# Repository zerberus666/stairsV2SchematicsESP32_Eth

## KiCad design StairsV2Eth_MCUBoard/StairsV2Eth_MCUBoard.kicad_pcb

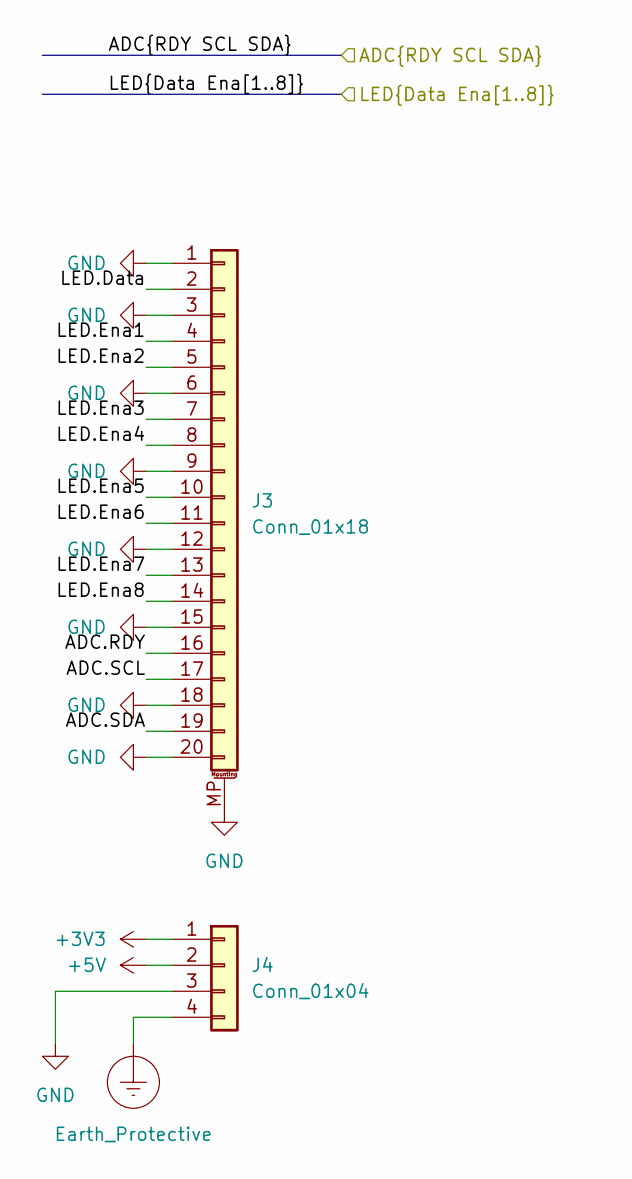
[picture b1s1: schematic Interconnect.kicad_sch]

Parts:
J3: Conn_01x18; FPC0520A1-20PVSZS1
J4: Conn_01x04; JST_XH_B4B-XH-AM_1x04_P2.50mm_Vertical

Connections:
+3V3: J4.1; also elsewhere on the board
+5V: J4.2
/ADC.RDY: J3.16
/ADC.SCL: J3.17
/ADC.SDA: J3.19
/LED.Data: J3.2; also elsewhere on the board
/LED.Ena1: J3.4; also elsewhere on the board
/LED.Ena2: J3.5; also elsewhere on the board
/LED.Ena3: J3.7; also elsewhere on the board
/LED.Ena4: J3.8; also elsewhere on the board
/LED.Ena5: J3.10; also elsewhere on the board
/LED.Ena6: J3.11; also elsewhere on the board
/LED.Ena7: J3.13; also elsewhere on the board
/LED.Ena8: J3.14; also elsewhere on the board
Earth_Protective: J4.4; also elsewhere on the board
GND: J3.1, J3.3, J3.6, J3.9, J3.12, J3.15, J3.18, J3.20, J3.MP (MountPin), J4.3; also elsewhere on the board

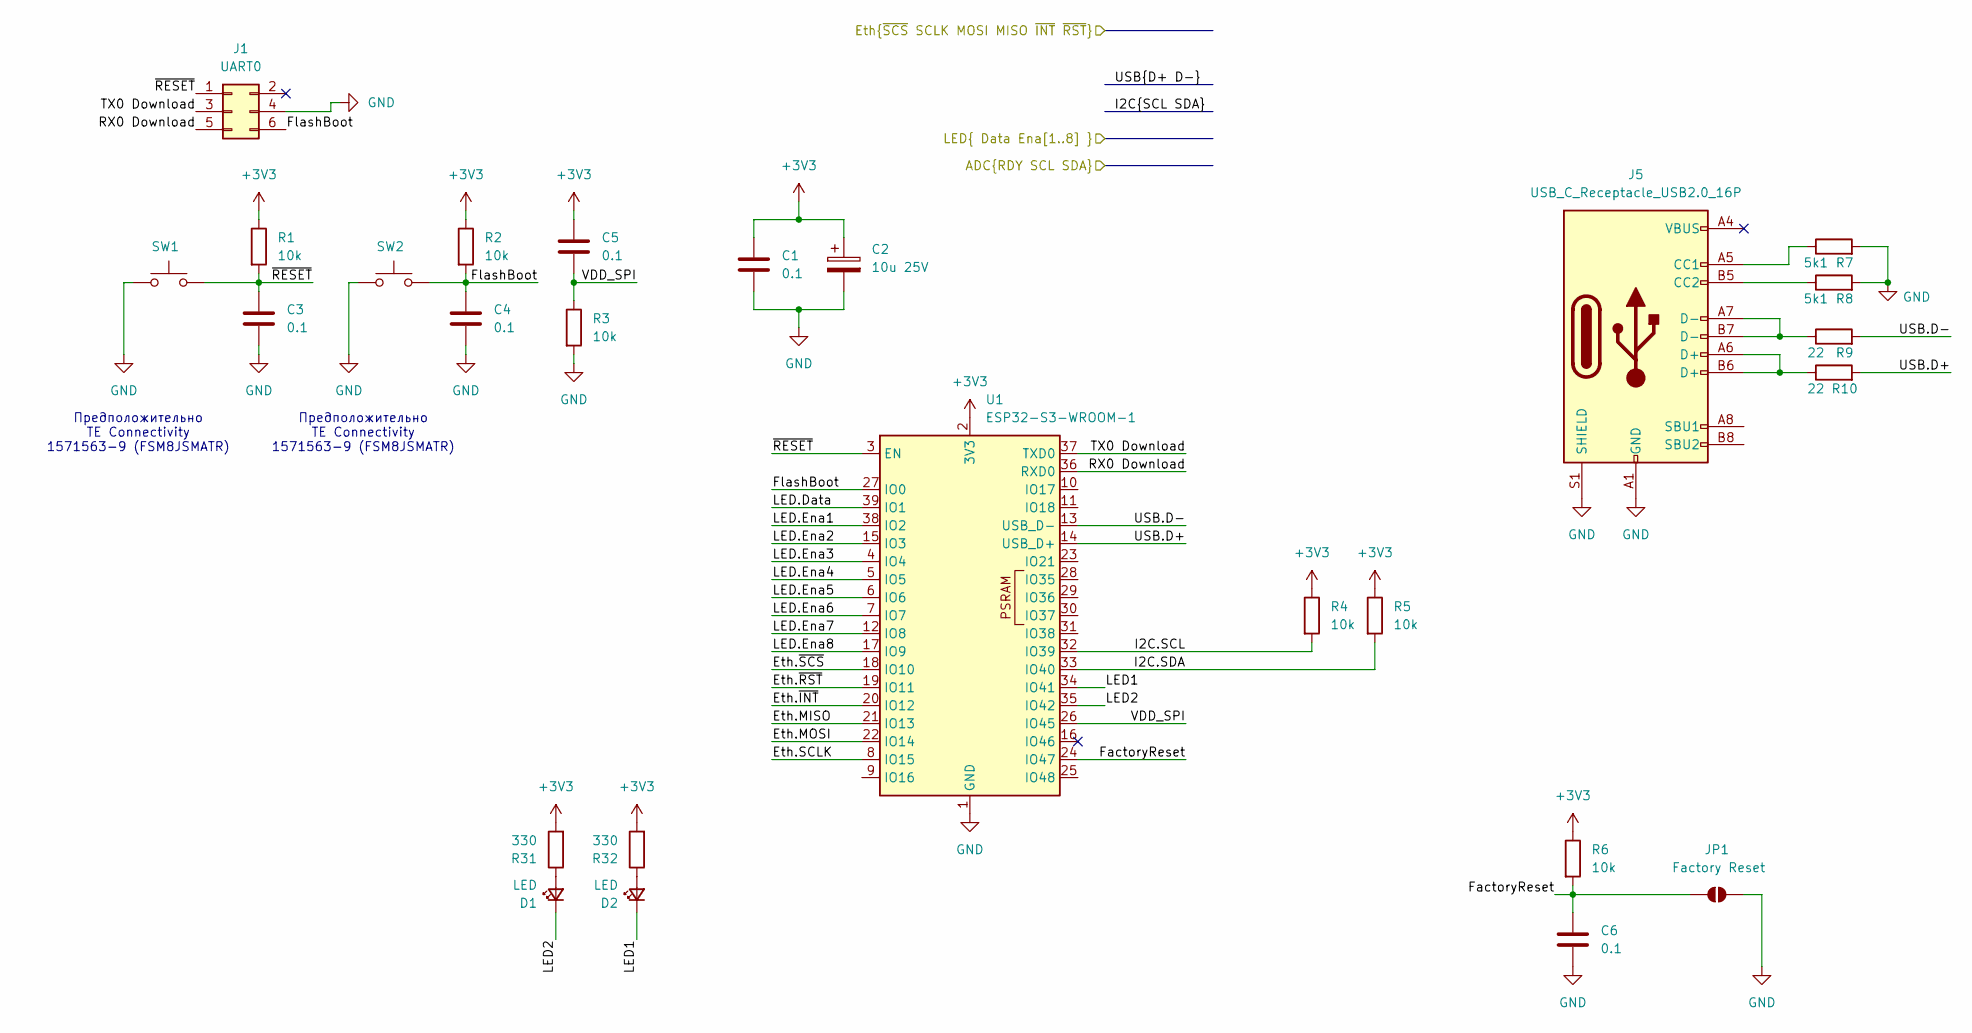
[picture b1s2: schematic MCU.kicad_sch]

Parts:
C1, C3, C4, C5, C6: 0.1; C_0805_2012Metric
C2: 10u 25V; CP_Elec_4x5.4
D1, D2: LED; LED_D3.0mm
J1: UART0; PinHeader_2x03_P1.27mm_Vertical_SMD
J5: USB_C_Receptacle_USB2.0_16P; USB_C_Receptacle_GCT_USB4110
JP1: Factory Reset; SolderJumper-2_P1.3mm_Open_RoundedPad1.0x1.5mm
R1, R2, R3, R4, R5, R6: 10k; R_0805_2012Metric
R7, R8: 5k1; R_0805_2012Metric
R9, R10: 22; R_0805_2012Metric
R31, R32: 330; R_0805_2012Metric
SW1, SW2: SW_Push; SW_Push_1P1T_NO_CK_KSC9xxJ
U1: ESP32-S3-WROOM-1

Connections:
+3V3: C1.1, C2.1, C5.1, R1.1, R2.1, R4.1, R5.1, R6.1, R31.2, R32.2, U1.2 (3V3); also elsewhere on the board
/Eth.MISO: U1.21 (IO13); also elsewhere on the board
/Eth.MOSI: U1.22 (IO14); also elsewhere on the board
/Eth.SCLK: U1.8 (IO15); also elsewhere on the board
/Eth.~INT: U1.20 (IO12); also elsewhere on the board
/Eth.~RST: U1.19 (IO11); also elsewhere on the board
/Eth.~SCS: U1.18 (IO10); also elsewhere on the board
/LED.Data: U1.39 (IO1); also elsewhere on the board
/LED.Ena1: U1.38 (IO2); also elsewhere on the board
/LED.Ena2: U1.15 (IO3); also elsewhere on the board
/LED.Ena3: U1.4 (IO4); also elsewhere on the board
/LED.Ena4: U1.5 (IO5); also elsewhere on the board
/LED.Ena5: U1.6 (IO6); also elsewhere on the board
/LED.Ena6: U1.7 (IO7); also elsewhere on the board
/LED.Ena7: U1.12 (IO8); also elsewhere on the board
/LED.Ena8: U1.17 (IO9); also elsewhere on the board
/MCU/FactoryReset: C6.1, JP1.1 (A), R6.2, U1.24 (IO47)
/MCU/FlashBoot: C4.1, J1.6, R2.2, SW2.2, U1.27 (IO0)
/MCU/I2C.SCL: R4.2, U1.32 (IO39)
/MCU/I2C.SDA: R5.2, U1.33 (IO40)
/MCU/LED1: D2.1 (K), U1.34 (IO41)
/MCU/LED2: D1.1 (K), U1.35 (IO42)
/MCU/RX0 Download: J1.5, U1.36 (RXD0)
/MCU/TX0 Download: J1.3, U1.37 (TXD0)
/MCU/USB.D+: R10.2, U1.14 (USB_D+)
/MCU/USB.D-: R9.2, U1.13 (USB_D-)
/MCU/VDD_SPI: C5.2, R3.1, U1.26 (IO45)
/MCU/~RESET: C3.1, J1.1, R1.2, SW1.2, U1.3 (EN)
GND: C1.2, C2.2, C3.2, C4.2, C6.2, J1.4, J5.A1 (GND), J5.A12 (GND), J5.B1 (GND), J5.B12 (GND), J5.S1 (SHIELD), JP1.2 (B), R3.2, R7.2, R8.2, SW1.1, SW2.1, U1.1 (GND), U1.40 (GND), U1.41 (GND); also elsewhere on the board
unnamed: D1.2 (A), R31.1
unnamed: D2.2 (A), R32.1
unnamed: J5.A5 (CC1), R7.1
unnamed: J5.B5 (CC2), R8.1
unnamed: J5.A6 (D+), J5.B6 (D+), R10.1
unnamed: J5.A7 (D-), J5.B7 (D-), R9.1

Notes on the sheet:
Предположительно TE Connectivity 1571563-9 (FSM8JSMATR)

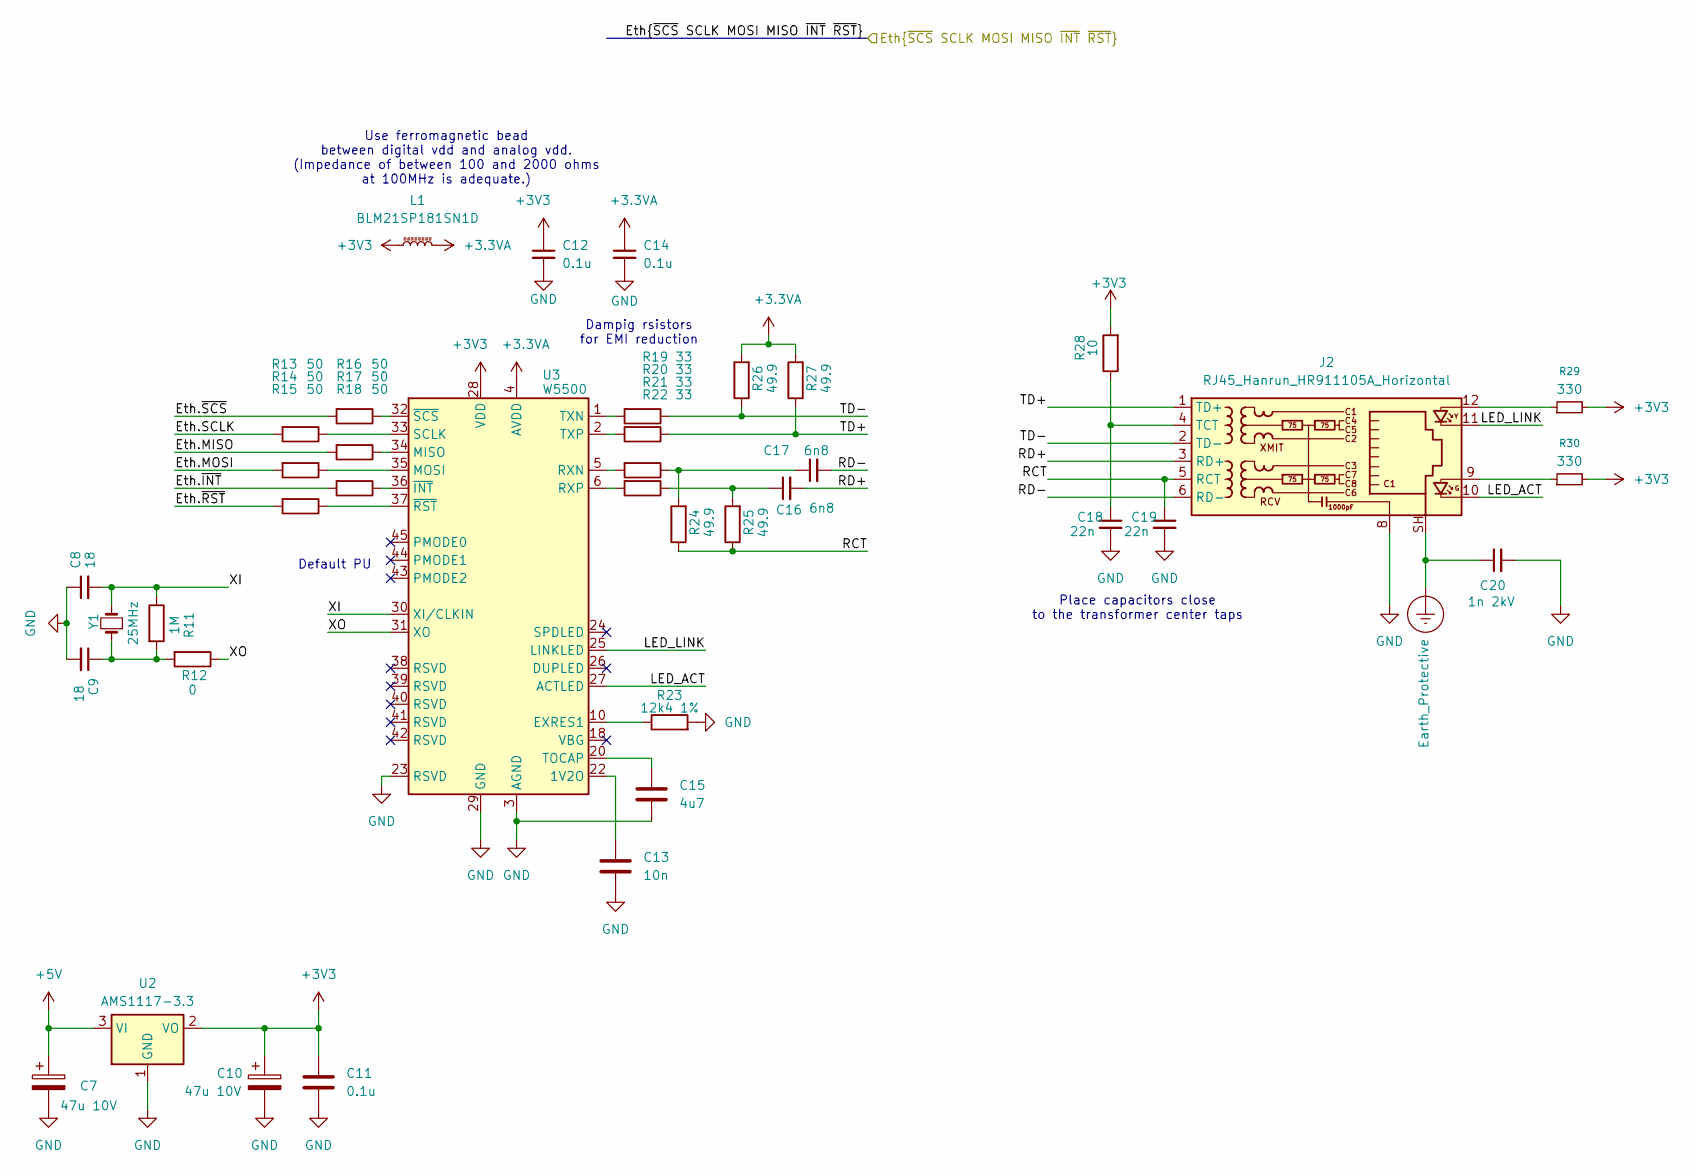
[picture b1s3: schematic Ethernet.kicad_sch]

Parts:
C7, C10: 47u 10V; CP_Elec_5x5.4
C8, C9: 18; C_0805_2012Metric
C11, C12, C14: 0.1u; C_0805_2012Metric
C13: 10n; C_0805_2012Metric
C15: 4u7; C_0805_2012Metric
C16, C17: 6n8; C_0805_2012Metric
C18, C19: 22n; C_0805_2012Metric
C20: 1n 2kV; C_Disc_D7.5mm_W2.5mm_P5.00mm
J2: RJ45_Hanrun_HR911105A_Horizontal
L1: BLM21SP181SN1D; L_0805_2012Metric
R11: 1M; R_0805_2012Metric
R12: 0; R_0805_2012Metric
R13, R14, R15, R16, R17, R18: 50; R_0805_2012Metric
R19, R20, R21, R22: 33; R_0805_2012Metric
R23: 12k4 1%; R_0805_2012Metric
R24, R25, R26, R27: 49.9; R_0805_2012Metric
R28: 10; R_0805_2012Metric
R29, R30: 330; R_0805_2012Metric
U2: AMS1117-3.3; SOT-223-3_TabPin2
U3: W5500; LQFP-48_7x7mm_P0.5mm
Y1: 25MHz; Crystal_SMD_Qantek_QC5CB-2Pin_5x3.2mm

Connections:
+3.3VA: C14.1, L1.2, R26.2, R27.2, U3.4 (AVDD), U3.8 (AVDD), U3.11 (AVDD), U3.15 (AVDD), U3.17 (AVDD), U3.21 (AVDD)
+3V3: C10.1, C11.1, C12.1, L1.1, R28.2, R29.2, R30.2, U2.2 (VO), U3.28 (VDD); also elsewhere on the board
/Eth.MISO: R17.2; also elsewhere on the board
/Eth.MOSI: R14.2; also elsewhere on the board
/Eth.SCLK: R13.2; also elsewhere on the board
/Eth.~INT: R18.2; also elsewhere on the board
/Eth.~RST: R15.2; also elsewhere on the board
/Eth.~SCS: R16.2; also elsewhere on the board
/Ethernet/LED_ACT: J2.10, U3.27 (ACTLED)
/Ethernet/LED_LINK: J2.11, U3.25 (LINKLED)
/Ethernet/RCT: C19.1, J2.5 (RCT), R24.1, R25.1
/Ethernet/RD+: C16.2, J2.3 (RD+)
/Ethernet/RD-: C17.2, J2.6 (RD-)
/Ethernet/TD+: J2.1 (TD+), R20.1, R27.1
/Ethernet/TD-: J2.2 (TD-), R19.1, R26.1
/Ethernet/XI: C8.2, R11.1, U3.30 (XI/CLKIN), Y1.2
/Ethernet/XO: R12.1, U3.31 (XO)
Earth_Protective: C20.1, J2.SH; also elsewhere on the board
GND: C7.2, C8.1, C9.2, C10.2, C11.2, C12.2, C13.2, C14.2, C15.2, C18.2, C19.2, C20.2, J2.8, R23.2, U2.1 (GND), U3.3 (AGND), U3.9 (AGND), U3.14 (AGND), U3.16 (AGND), U3.19 (AGND), U3.23 (RSVD), U3.29 (GND), U3.48 (AGND); also elsewhere on the board
unnamed: C7.1, U2.3 (VI)
unnamed: C9.1, R11.2, R12.2, Y1.1
unnamed: C16.1, R22.1, R25.2
unnamed: C17.1, R21.1, R24.2
unnamed: J2.9, R30.1
unnamed: J2.12, R29.1
unnamed: C18.1, J2.4 (TCT), R28.1
unnamed: C13.1, U3.22 (1V2O)
unnamed: R23.1, U3.10 (EXRES1)
unnamed: R17.1, U3.34 (MISO)
unnamed: R14.1, U3.35 (MOSI)
unnamed: R21.2, U3.5 (RXN)
unnamed: R22.2, U3.6 (RXP)
unnamed: R13.1, U3.33 (SCLK)
unnamed: C15.1, U3.20 (TOCAP)
unnamed: R19.2, U3.1 (TXN)
unnamed: R20.2, U3.2 (TXP)
unnamed: R18.1, U3.36 (~INT)
unnamed: R15.1, U3.37 (~RST)
unnamed: R16.1, U3.32 (~SCS)

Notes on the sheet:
Dampig rsistors for EMI reduction
Use ferromagnetic bead between digital vdd and analog vdd. (Impedance of between 100 and 2000 ohms at 100MHz is adequate.)
Place capacitors close to the transformer center taps
Default PU

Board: 2 copper layers, 61 parts (57 on the bottom side), 65 nets, no tracks yet.

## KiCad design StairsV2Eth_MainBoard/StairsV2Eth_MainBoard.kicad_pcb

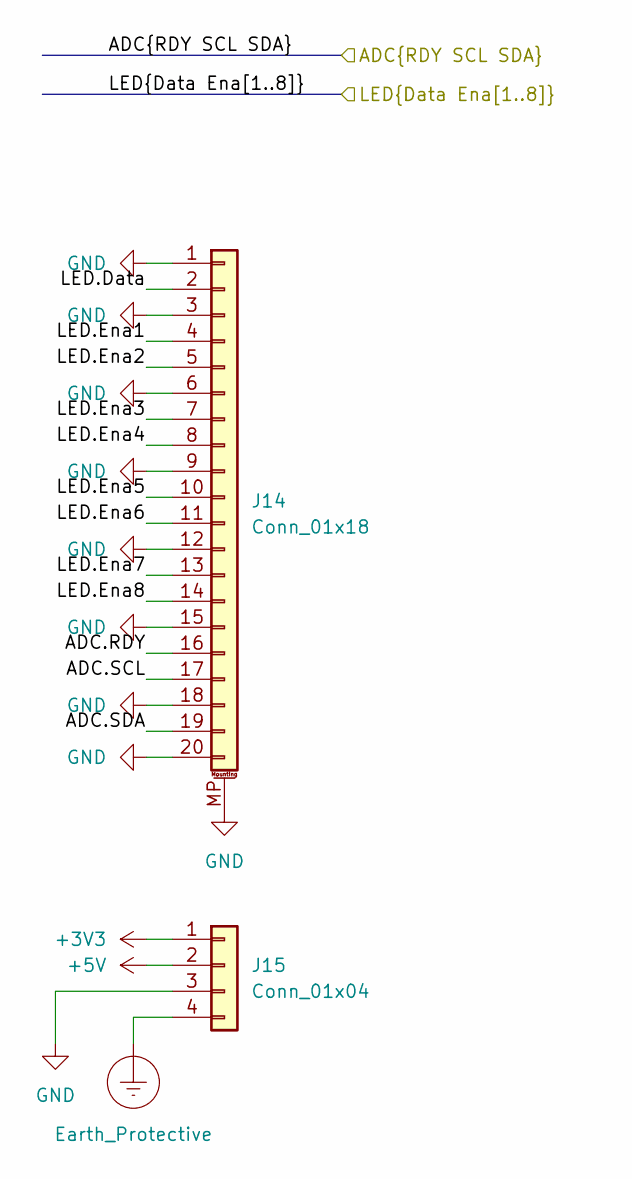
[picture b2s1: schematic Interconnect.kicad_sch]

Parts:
J14: Conn_01x18; FPC0520A1-20PVSZS1
J15: Conn_01x04; JST_XH_B4B-XH-AM_1x04_P2.50mm_Vertical

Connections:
+3V3: J15.1; also elsewhere on the board
+5V: J15.2; also elsewhere on the board
/ADC.RDY: J14.16; also elsewhere on the board
/ADC.SCL: J14.17; also elsewhere on the board
/ADC.SDA: J14.19; also elsewhere on the board
/LED.Data: J14.2; also elsewhere on the board
/LED.Ena1: J14.4; also elsewhere on the board
/LED.Ena2: J14.5; also elsewhere on the board
/LED.Ena3: J14.7; also elsewhere on the board
/LED.Ena4: J14.8; also elsewhere on the board
/LED.Ena5: J14.10; also elsewhere on the board
/LED.Ena6: J14.11; also elsewhere on the board
/LED.Ena7: J14.13; also elsewhere on the board
/LED.Ena8: J14.14; also elsewhere on the board
Earth_Protective: J15.4; also elsewhere on the board
GND: J14.1, J14.3, J14.6, J14.9, J14.12, J14.15, J14.18, J14.20, J14.MP (MountPin), J15.3; also elsewhere on the board

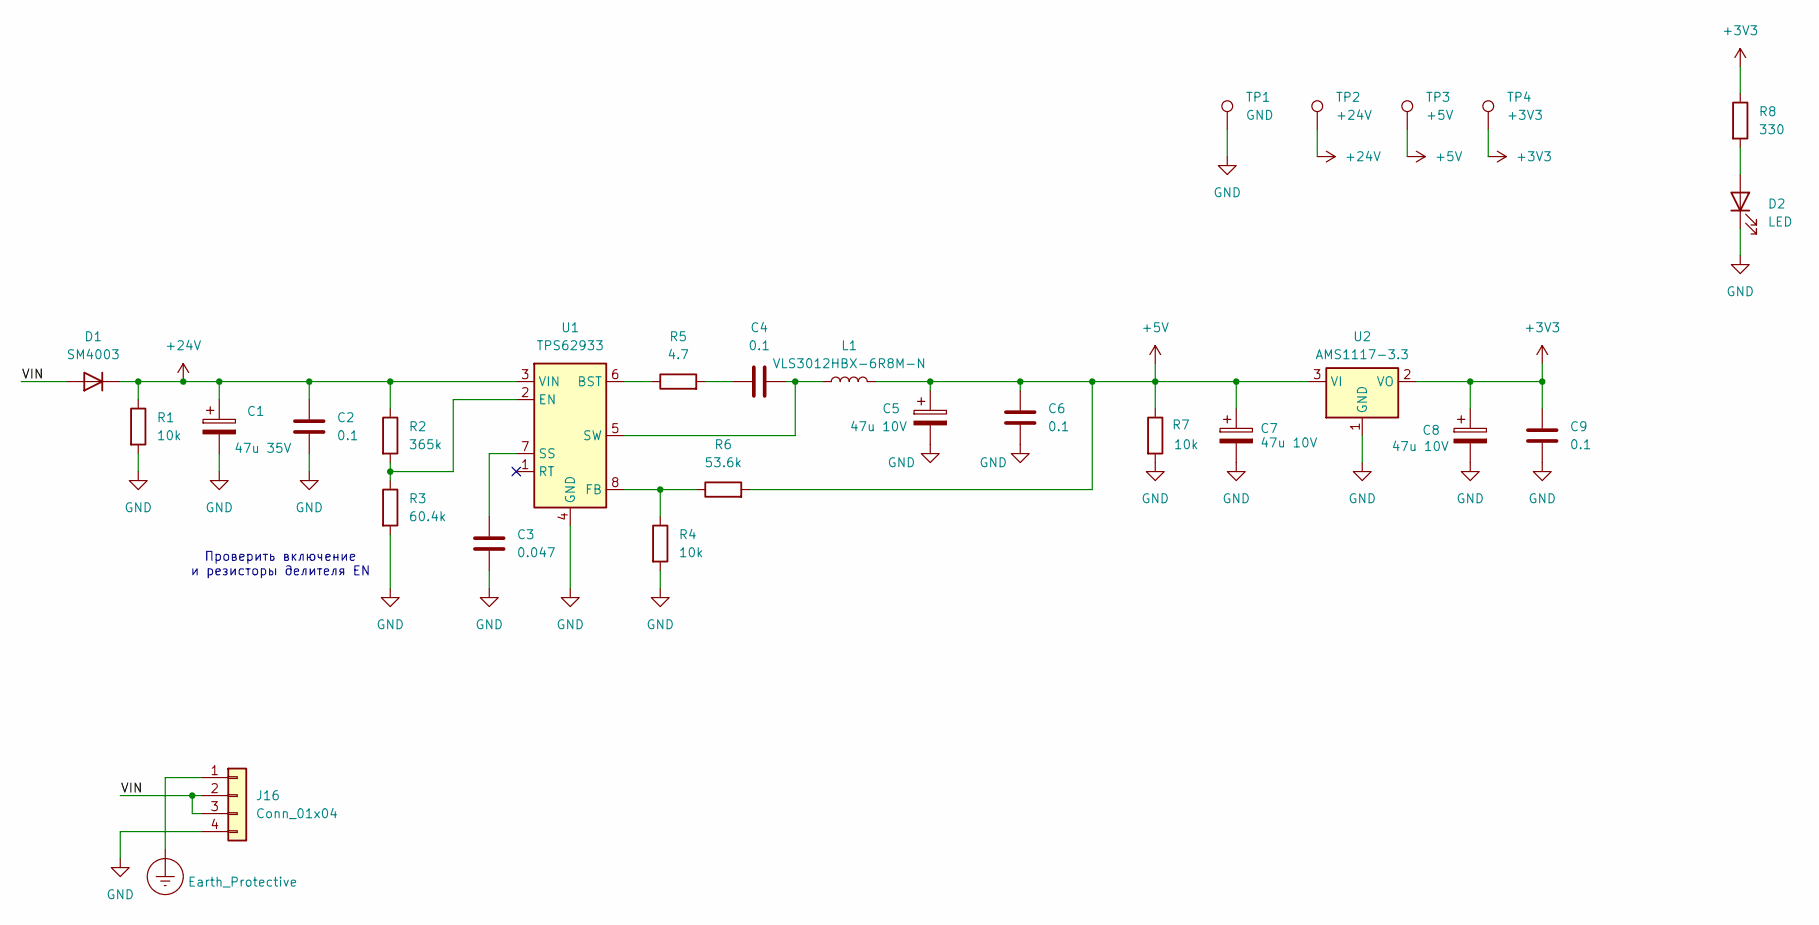
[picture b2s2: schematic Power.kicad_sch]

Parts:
C1: 47u 35V; CP_Elec_6.3x5.4
C2, C4, C6, C9: 0.1; C_0805_2012Metric
C3: 0.047; C_0805_2012Metric
C5, C7, C8: 47u 10V; CP_Elec_5x5.4
D1: SM4003; D_MELF
D2: LED; LED_0805_2012Metric
J16: Conn_01x04; PhoenixContact_MCV_1,5_4-G-3.5_1x04_P3.50mm_Vertical
L1: VLS3012HBX-6R8M-N; IND_VLS3012HBX-6R8M-N
R1, R4, R7: 10k; R_0805_2012Metric
R2: 365k; R_0805_2012Metric
R3: 60.4k; R_0805_2012Metric
R5: 4.7; R_0805_2012Metric
R6: 53.6k; R_0805_2012Metric
R8: 330; R_0805_2012Metric
TP1: GND; TestPoint_Pad_1.0x1.0mm
TP2: +24V; TestPoint_Pad_1.0x1.0mm
TP3: +5V; TestPoint_Pad_1.0x1.0mm
TP4: +3V3; TestPoint_Pad_1.0x1.0mm
U1: TPS62933; SOT-583-8
U2: AMS1117-3.3; SOT-223-3_TabPin2

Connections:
+3V3: C8.1, C9.1, R8.1, TP4.1, U2.2 (VO); also elsewhere on the board
+5V: C5.1, C6.1, C7.1, L1.2, R6.2, R7.1, TP3.1, U2.3 (VI); also elsewhere on the board
+24V: C1.1, C2.1, D1.1 (K), R1.1, R2.1, TP2.1, U1.3 (VIN); also elsewhere on the board
/Power/VIN: D1.2 (A), J16.2, J16.3
Earth_Protective: J16.1; also elsewhere on the board
GND: C1.2, C2.2, C3.2, C5.2, C6.2, C7.2, C8.2, C9.2, D2.1 (K), J16.4, R1.2, R3.2, R4.2, R7.2, TP1.1, U1.4 (GND), U2.1 (GND); also elsewhere on the board
unnamed: C4.1, R5.2
unnamed: D2.2 (A), R8.2
unnamed: R5.1, U1.6 (BST)
unnamed: R2.2, R3.1, U1.2 (EN)
unnamed: R4.1, R6.1, U1.8 (FB)
unnamed: C3.1, U1.7 (SS)
unnamed: C4.2, L1.1, U1.5 (SW)

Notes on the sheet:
Проверить включение и резисторы делителя EN

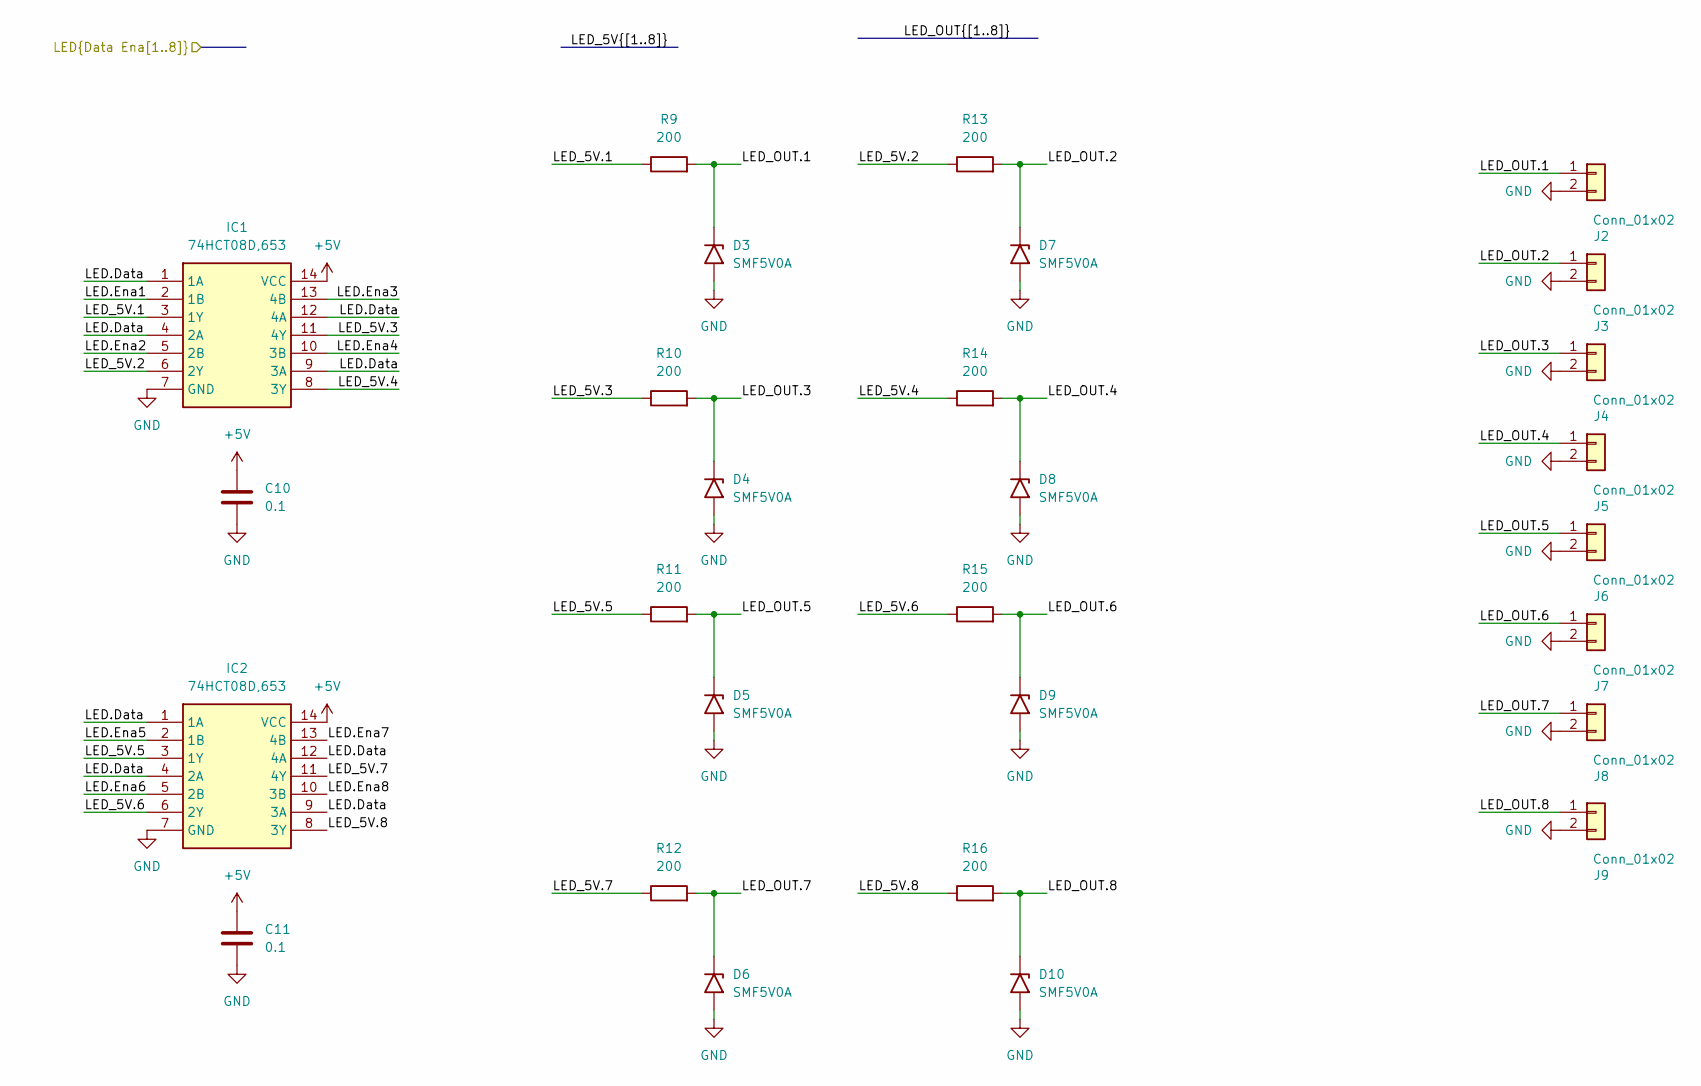
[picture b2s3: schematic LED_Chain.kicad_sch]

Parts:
C10, C11: 0.1; C_0805_2012Metric
D3, D4, D5, D6, D7, D8, D9, D10: SMF5V0A; D_SMF
IC1, IC2: 74HCT08D,653; SOIC127P600X175-14N; Manufacturer_Part_Number 74HCT08D,653; Mouser Part Number 771-74HCT08D-T
J2, J3, J4, J5, J6, J7, J8, J9: Conn_01x02; PhoenixContact_MCV_1,5_2-G-3.5_1x02_P3.50mm_Vertical
R9, R10, R11, R12, R13, R14, R15, R16: 200; R_0805_2012Metric

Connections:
+5V: C10.1, C11.1, IC1.14 (VCC), IC2.14 (VCC); also elsewhere on the board
/LED Chain/LED_5V.1: IC1.3 (1Y), R9.1
/LED Chain/LED_5V.2: IC1.6 (2Y), R13.1
/LED Chain/LED_5V.3: IC1.11 (4Y), R10.1
/LED Chain/LED_5V.4: IC1.8 (3Y), R14.1
/LED Chain/LED_5V.5: IC2.3 (1Y), R11.1
/LED Chain/LED_5V.6: IC2.6 (2Y), R15.1
/LED Chain/LED_5V.7: IC2.11 (4Y), R12.1
/LED Chain/LED_5V.8: IC2.8 (3Y), R16.1
/LED Chain/LED_OUT.1: D3.1 (A1), J2.1, R9.2
/LED Chain/LED_OUT.2: D7.1 (A1), J3.1, R13.2
/LED Chain/LED_OUT.3: D4.1 (A1), J4.1, R10.2
/LED Chain/LED_OUT.4: D8.1 (A1), J5.1, R14.2
/LED Chain/LED_OUT.5: D5.1 (A1), J6.1, R11.2
/LED Chain/LED_OUT.6: D9.1 (A1), J7.1, R15.2
/LED Chain/LED_OUT.7: D6.1 (A1), J8.1, R12.2
/LED Chain/LED_OUT.8: D10.1 (A1), J9.1, R16.2
/LED.Data: IC1.1 (1A), IC1.4 (2A), IC1.9 (3A), IC1.12 (4A), IC2.1 (1A), IC2.4 (2A), IC2.9 (3A), IC2.12 (4A); also elsewhere on the board
/LED.Ena1: IC1.2 (1B); also elsewhere on the board
/LED.Ena2: IC1.5 (2B); also elsewhere on the board
/LED.Ena3: IC1.13 (4B); also elsewhere on the board
/LED.Ena4: IC1.10 (3B); also elsewhere on the board
/LED.Ena5: IC2.2 (1B); also elsewhere on the board
/LED.Ena6: IC2.5 (2B); also elsewhere on the board
/LED.Ena7: IC2.13 (4B); also elsewhere on the board
/LED.Ena8: IC2.10 (3B); also elsewhere on the board
GND: C10.2, C11.2, D3.2 (A2), D4.2 (A2), D5.2 (A2), D6.2 (A2), D7.2 (A2), D8.2 (A2), D9.2 (A2), D10.2 (A2), IC1.7 (GND), IC2.7 (GND), J2.2, J3.2, J4.2, J5.2, J6.2, J7.2, J8.2, J9.2; also elsewhere on the board

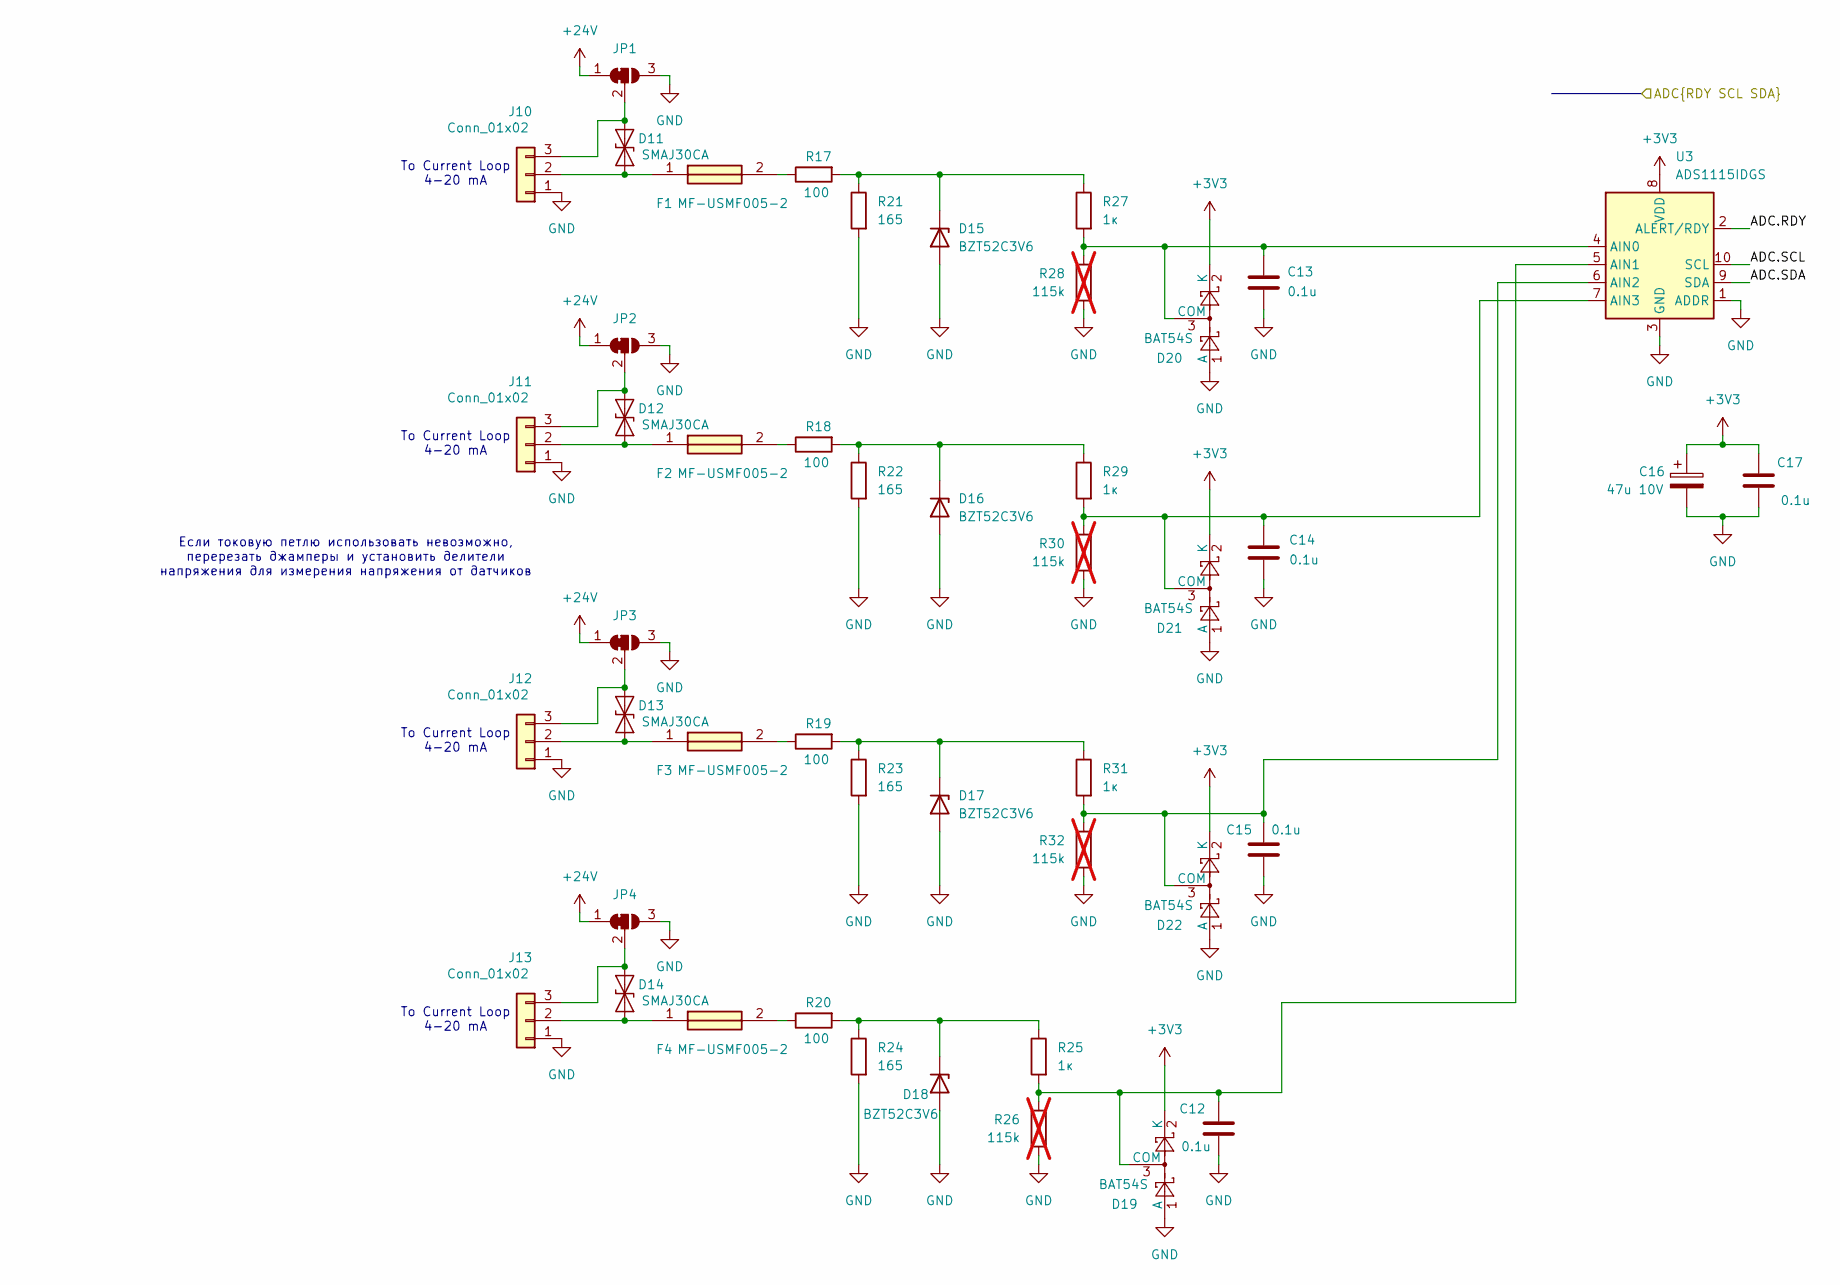
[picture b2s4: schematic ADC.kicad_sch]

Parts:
C12, C13, C14, C15, C17: 0.1u; C_0805_2012Metric
C16: 47u 10V; CP_Elec_5x5.4
D11, D12, D13, D14: SMAJ30CA; D_SMA
D15, D16, D17, D18: BZT52C3V6; D_SOD-123F
D19, D20, D21, D22: BAT54S; SOT-23
F1, F2, F3, F4: MF-USMF005-2; FUSC3226X110N; Manufacturer_Part_Number MF-USMF005-2; Mouser Part Number 652-MF-USMF005-2
J10, J11, J12, J13: Conn_01x02; PhoenixContact_MCV_1,5_3-G-3.5_1x03_P3.50mm_Vertical
JP1, JP2, JP3, JP4: SolderJumper_3_Bridged12; SolderJumper-3_P1.3mm_Bridged12_RoundedPad1.0x1.5mm
R17, R18, R19, R20: 100; R_1206_3216Metric
R21, R22, R23, R24: 165; R_1206_3216Metric
R25, R27, R29, R31: 1к; R_0805_2012Metric
R26, R28, R30, R32: 115k; R_0805_2012Metric; not fitted
U3: ADS1115IDGS; TSSOP-10_3x3mm_P0.5mm

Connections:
+3V3: C16.1, C17.1, D19.2 (K), D20.2 (K), D21.2 (K), D22.2 (K), U3.8 (VDD); also elsewhere on the board
+24V: JP1.1 (A), JP2.1 (A), JP3.1 (A), JP4.1 (A); also elsewhere on the board
/ADC.RDY: U3.2 (ALERT/RDY); also elsewhere on the board
/ADC.SCL: U3.10 (SCL); also elsewhere on the board
/ADC.SDA: U3.9 (SDA); also elsewhere on the board
GND: C12.2, C13.2, C14.2, C15.2, C16.2, C17.2, D15.2 (A), D16.2 (A), D17.2 (A), D18.2 (A), D19.1 (A), D20.1 (A), D21.1 (A), D22.1 (A), J10.1, J11.1, J12.1, J13.1, JP1.3 (B), JP2.3 (B), JP3.3 (B), JP4.3 (B), R21.2, R22.2, R23.2, R24.2, R26.2, R28.2, R30.2, R32.2, U3.1 (ADDR), U3.3 (GND); also elsewhere on the board
unnamed: D11.1 (A1), F1.1, J10.2
unnamed: D11.2 (A2), J10.3, JP1.2 (C)
unnamed: D12.1 (A1), F2.1, J11.2
unnamed: D12.2 (A2), J11.3, JP2.2 (C)
unnamed: D13.1 (A1), F3.1, J12.2
unnamed: D13.2 (A2), J12.3, JP3.2 (C)
unnamed: D14.1 (A1), F4.1, J13.2
unnamed: D14.2 (A2), J13.3, JP4.2 (C)
unnamed: D15.1 (K), R17.2, R21.1, R27.1
unnamed: D16.1 (K), R18.2, R22.1, R29.1
unnamed: D17.1 (K), R19.2, R23.1, R31.1
unnamed: D18.1 (K), R20.2, R24.1, R25.1
unnamed: C12.1, D19.3 (COM), R25.2, R26.1, U3.5 (AIN1)
unnamed: C13.1, D20.3 (COM), R27.2, R28.1, U3.4 (AIN0)
unnamed: C14.1, D21.3 (COM), R29.2, R30.1, U3.7 (AIN3)
unnamed: C15.1, D22.3 (COM), R31.2, R32.1, U3.6 (AIN2)
unnamed: F1.2, R17.1
unnamed: F2.2, R18.1
unnamed: F3.2, R19.1
unnamed: F4.2, R20.1

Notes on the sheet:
To Current Loop 4-20 mA
Если токовую петлю использовать невозможно, перерезать джамперы и установить делители напряжения для измерения напряжения от датчиков

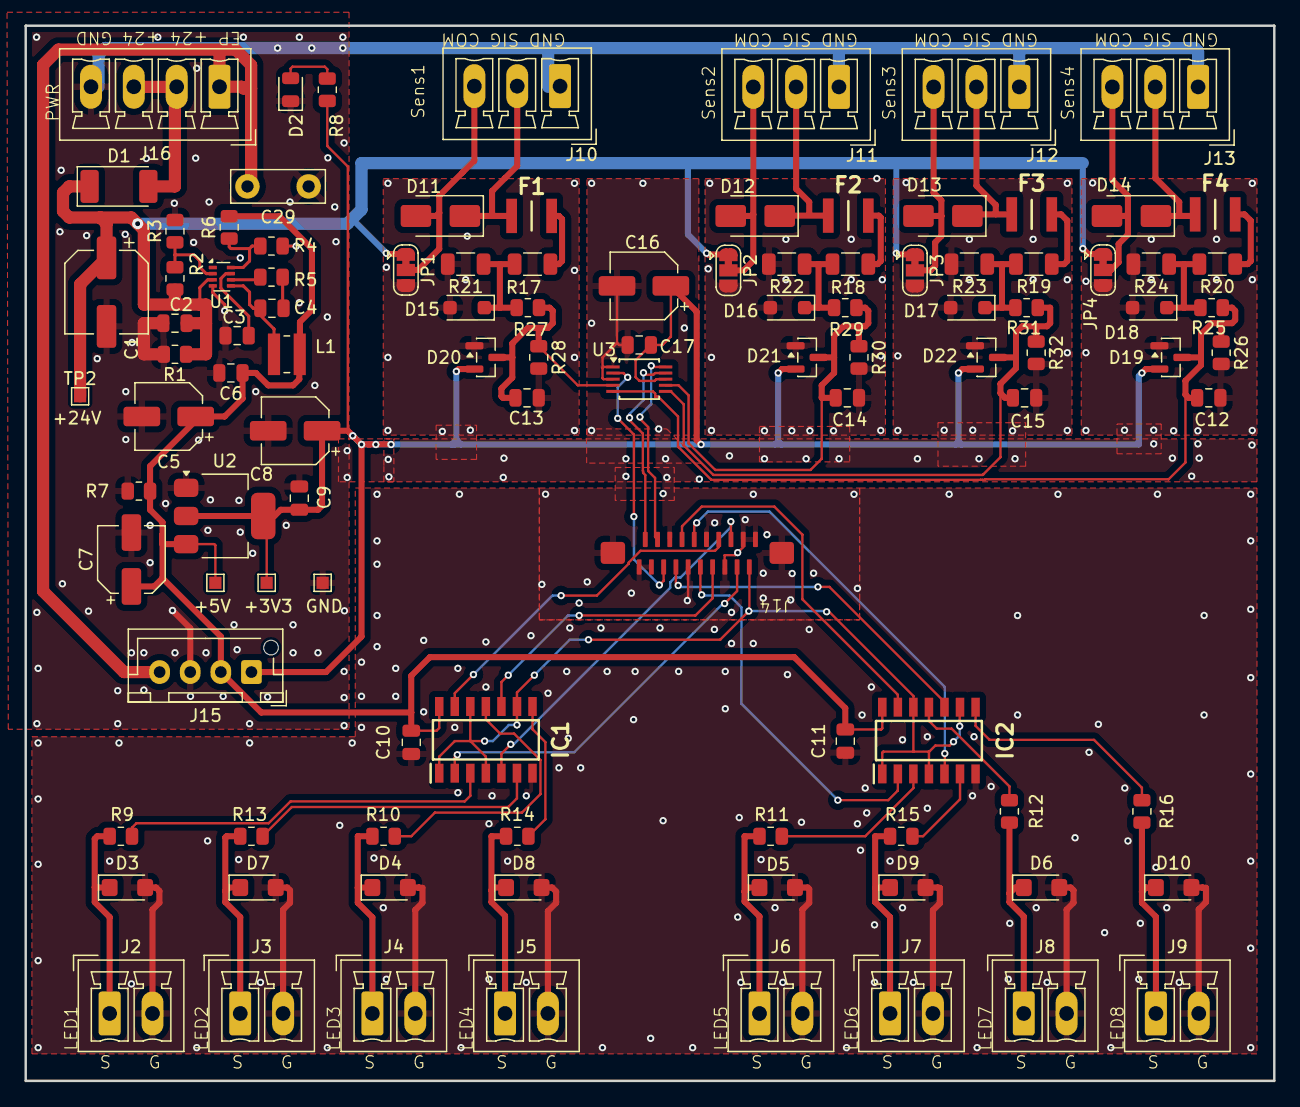
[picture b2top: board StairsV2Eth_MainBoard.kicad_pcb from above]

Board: 2 copper layers, 102.0 x 86.2 mm, 105 parts (0 on the bottom side), 61 nets.

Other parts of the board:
C29: 1n 2kV; C_Disc_D7.5mm_W2.5mm_P5.00mm

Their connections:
Earth_Protective: C29.2; also elsewhere on the board
GND: C29.1; also elsewhere on the board

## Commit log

2025-12-05 Ethernet PHY scheme
2025-12-09 Ethernet W55000 controller added
2025-12-16 Mainvoard PCB Added
2025-12-18 Ethernet on the MCU Board
